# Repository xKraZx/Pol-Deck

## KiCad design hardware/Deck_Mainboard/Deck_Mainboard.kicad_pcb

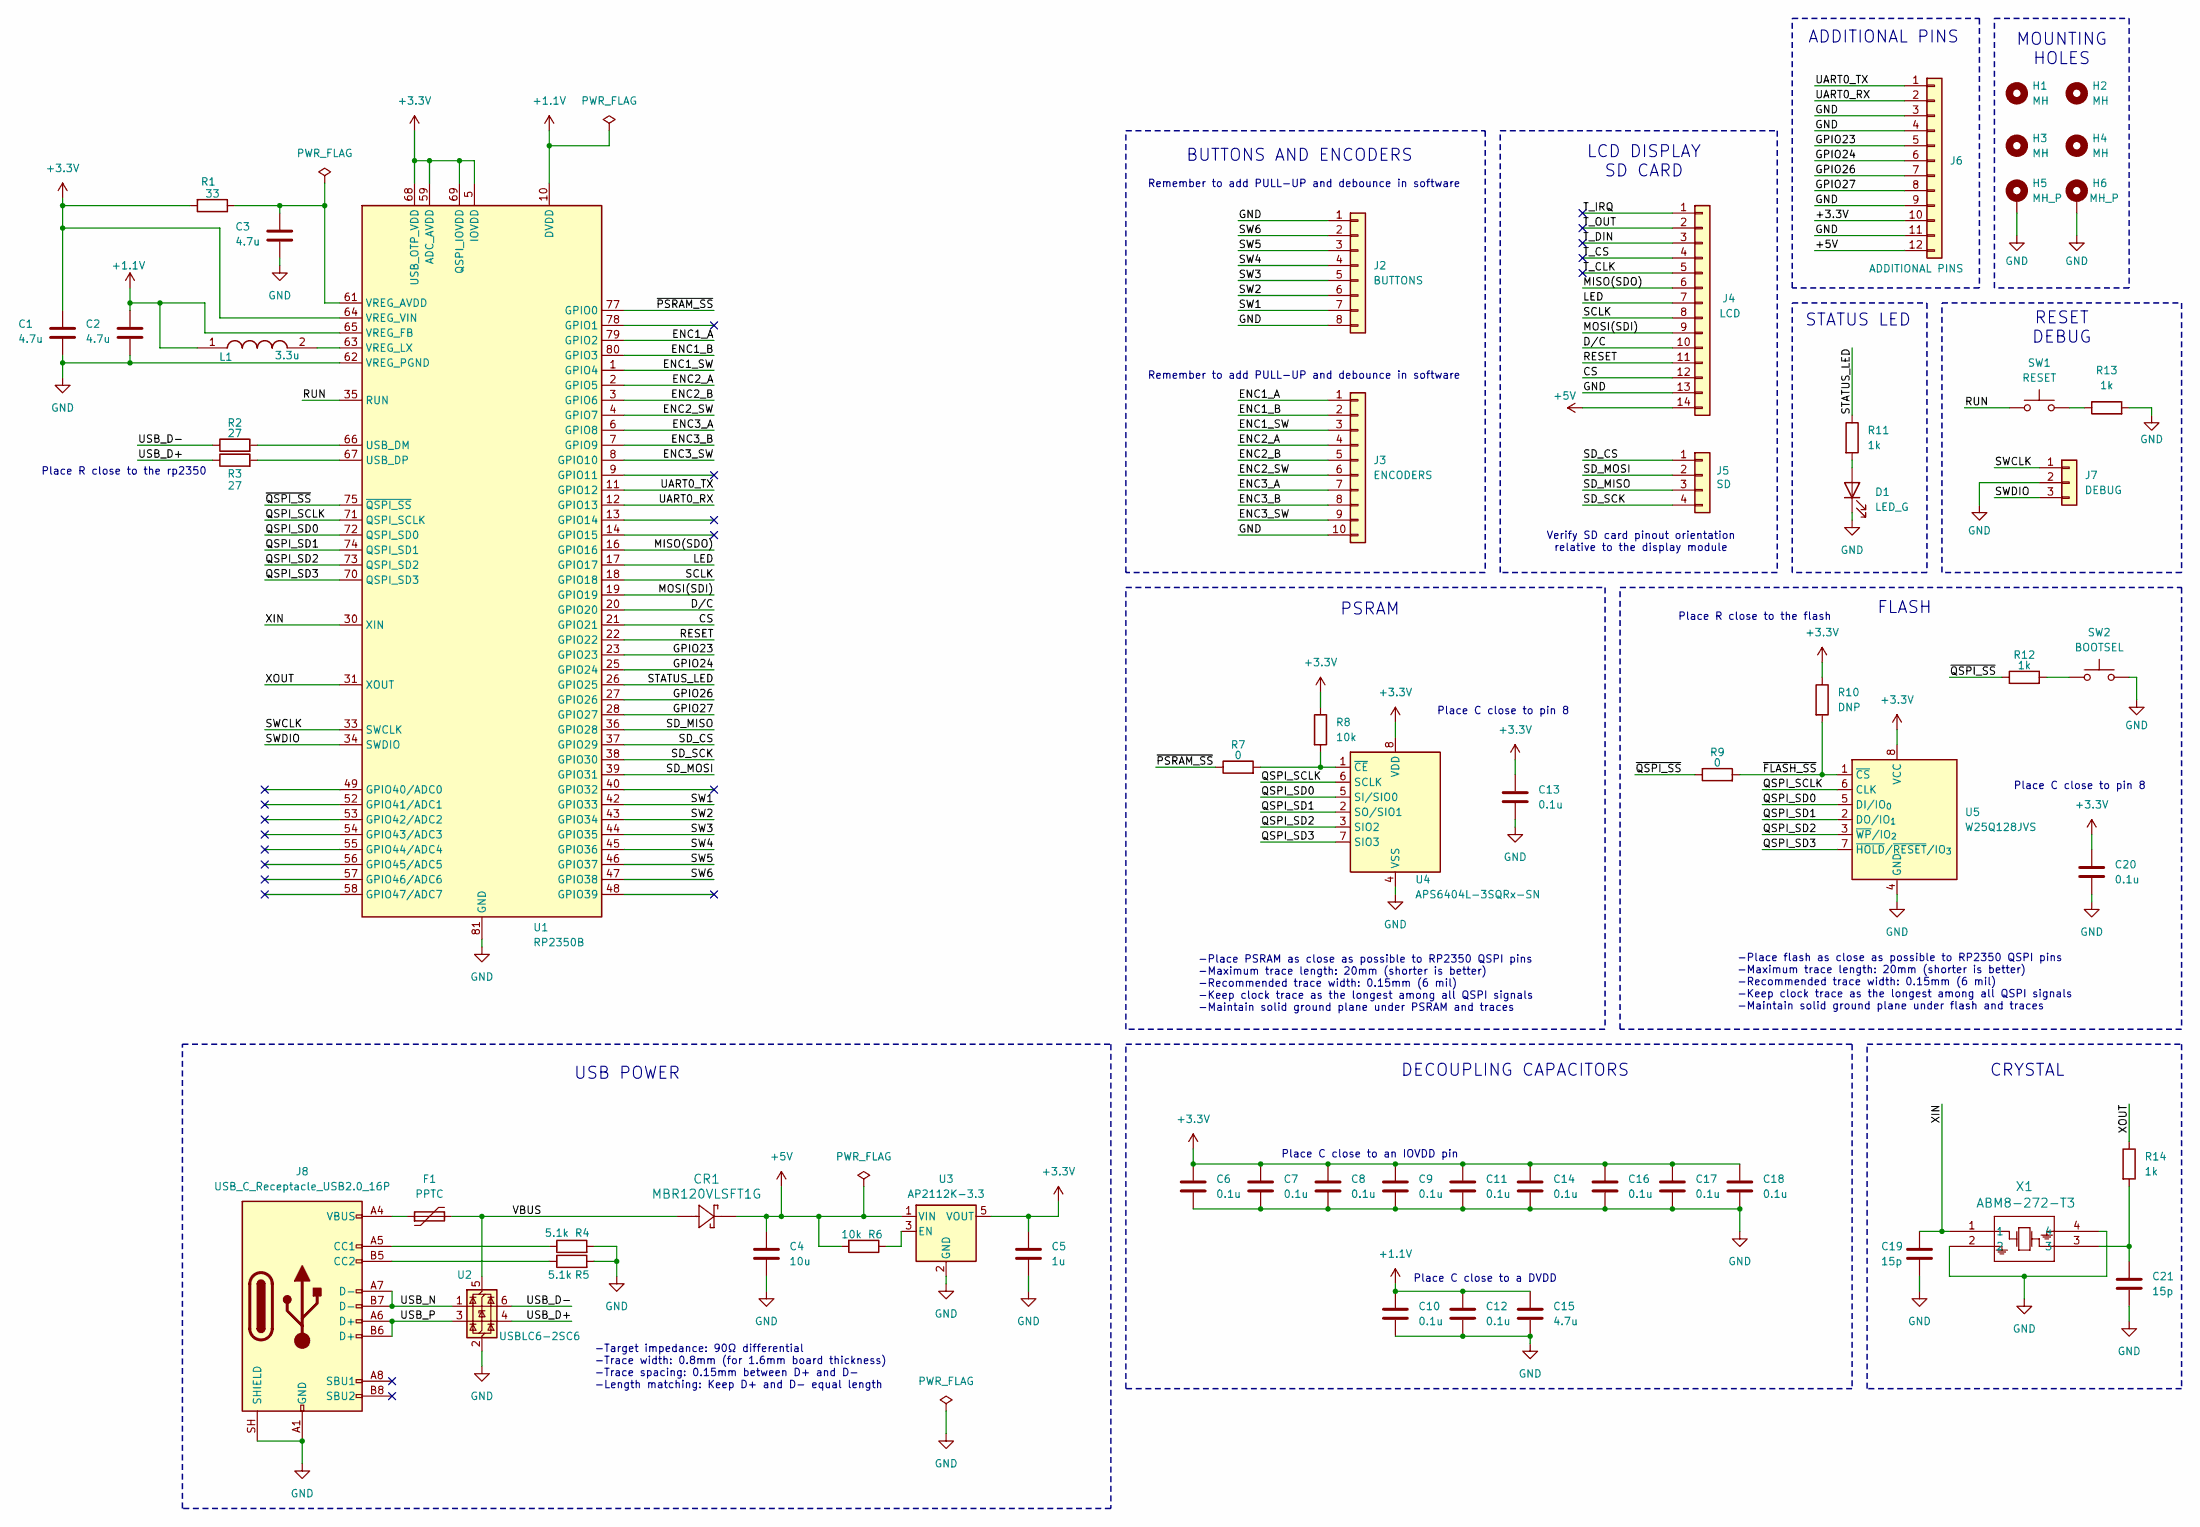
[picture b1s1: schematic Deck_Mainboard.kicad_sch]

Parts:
C1, C2, C3, C15: 4.7u; C_0402_1005Metric_Pad0.74x0.62mm_HandSolder
C4: 10u; C_0402_1005Metric_Pad0.74x0.62mm_HandSolder
C5: 1u; C_0402_1005Metric_Pad0.74x0.62mm_HandSolder
C6, C7, C8, C9, C10, C11, C12, C13, C14, C16, C17, C18, C20: 0.1u; C_0402_1005Metric_Pad0.74x0.62mm_HandSolder
C19, C21: 15p; C_0402_1005Metric_Pad0.74x0.62mm_HandSolder
CR1: MBR120VLSFT1G
D1: LED_G; LED_0603_1608Metric_Pad1.05x0.95mm_HandSolder
F1: PPTC; Fuse_1812_4532Metric_Pad1.30x3.40mm_HandSolder
H1, H2, H3, H4: MH; MountingHole_3.2mm_M3
H5, H6: MH_P; MountingHole_3.2mm_M3_Pad
J2: BUTTONS; PinHeader_1x08_P2.54mm_Vertical
J3: ENCODERS; PinHeader_1x10_P2.54mm_Vertical
J4: LCD; PinHeader_1x14_P2.54mm_Vertical
J5: SD; PinHeader_1x04_P2.54mm_Vertical
J6: ADDITIONAL PINS; PinHeader_1x12_P2.54mm_Vertical
J7: DEBUG; PinHeader_1x03_P2.54mm_Vertical
J8: USB_C_Receptacle_USB2.0_16P; USB_C_vertical
L1: 3.3u; AOTAB201610S3R3101T; Manufacturer_Part_Number AOTA-B201610S3R3-101-T
R1: 33; R_0402_1005Metric_Pad0.72x0.64mm_HandSolder
R2, R3: 27; R_0402_1005Metric_Pad0.72x0.64mm_HandSolder
R4, R5: 5.1k; R_0402_1005Metric_Pad0.72x0.64mm_HandSolder
R6, R8: 10k; R_0402_1005Metric_Pad0.72x0.64mm_HandSolder
R7, R9: 0; R_0402_1005Metric_Pad0.72x0.64mm_HandSolder
R10: DNP; R_0402_1005Metric_Pad0.72x0.64mm_HandSolder
R11, R12, R13, R14: 1k; R_0402_1005Metric_Pad0.72x0.64mm_HandSolder
SW1: RESET; SW_Push_1P1T_NO_E-Switch_TL3301NxxxxxG
SW2: BOOTSEL; SW_Push_1P1T_NO_E-Switch_TL3301NxxxxxG
U1: RP2350B; QFN-80-1EP_10x10mm_P0.4mm_EP3.4x3.4mm
U2: USBLC6-2SC6; SOT-23-6
U3: AP2112K-3.3; SOT-23-5
U4: APS6404L-3SQRx-SN; SOIC-8_3.9x4.9mm_P1.27mm
U5: W25Q128JVS; SOIC-8_5.3x5.3mm_P1.27mm
X1: ABM8-272-T3; ABM8-272-T3_ABR

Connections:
+1.1V: C2.1, C10.1, C12.1, C15.1, L1.1, U1.10 (DVDD), U1.32 (DVDD), U1.51 (DVDD), U1.65 (VREG_FB)
+3.3V: C1.1, C5.1, C6.1, C7.1, C8.1, C9.1, C11.1, C13.1, C14.1, C16.1, C17.1, C18.1, C20.1, J6.10, R1.2, R8.1, R10.1, U1.5 (IOVDD), U1.15 (IOVDD), U1.24 (IOVDD), U1.29 (IOVDD), U1.41 (IOVDD), U1.50 (IOVDD), U1.59 (ADC_AVDD), U1.60 (IOVDD), U1.64 (VREG_VIN), U1.68 (USB_OTP_VDD), U1.69 (QSPI_IOVDD), U1.76 (IOVDD), U3.5 (VOUT), U4.8 (VDD), U5.8 (VCC)
+5V: C4.1, CR1.1, J4.14, J6.12, R6.2, U3.1 (VIN)
/CS: J4.12, U1.21 (GPIO21)
/D/C: J4.10, U1.20 (GPIO20)
/ENC1_A: J3.1, U1.79 (GPIO2)
/ENC1_B: J3.2, U1.80 (GPIO3)
/ENC1_SW: J3.3, U1.1 (GPIO4)
/ENC2_A: J3.4, U1.2 (GPIO5)
/ENC2_B: J3.5, U1.3 (GPIO6)
/ENC2_SW: J3.6, U1.4 (GPIO7)
/ENC3_A: J3.7, U1.6 (GPIO8)
/ENC3_B: J3.8, U1.7 (GPIO9)
/ENC3_SW: J3.9, U1.8 (GPIO10)
/GPIO23: J6.5, U1.23 (GPIO23)
/GPIO24: J6.6, U1.25 (GPIO24)
/GPIO26: J6.7, U1.27 (GPIO26)
/GPIO27: J6.8, U1.28 (GPIO27)
/LED: J4.7, U1.17 (GPIO17)
/MISO(SDO): J4.6, U1.16 (GPIO16)
/MOSI(SDI): J4.9, U1.19 (GPIO19)
/QSPI_SCLK: U1.71 (QSPI_SCLK), U4.6 (SCLK), U5.6 (CLK)
/QSPI_SD0: U1.72 (QSPI_SD0), U4.5 (SI/SIO0), U5.5 (DI/IO_{0})
/QSPI_SD1: U1.74 (QSPI_SD1), U4.2 (SO/SIO1), U5.2 (DO/IO_{1})
/QSPI_SD2: U1.73 (QSPI_SD2), U4.3 (SIO2), U5.3 (~WP/IO_{2})
/QSPI_SD3: U1.70 (QSPI_SD3), U4.7 (SIO3), U5.7 (~HOLD/~RESET/IO_{3})
/RESET: J4.11, U1.22 (GPIO22)
/RUN: SW1.1, U1.35 (RUN)
/SCLK: J4.8, U1.18 (GPIO18)
/SD_CS: J5.1, U1.37 (GPIO29)
/SD_MISO: J5.3, U1.36 (GPIO28)
/SD_MOSI: J5.2, U1.39 (GPIO31)
/SD_SCK: J5.4, U1.38 (GPIO30)
/STATUS_LED: R11.1, U1.26 (GPIO25)
/SW1: J2.7, U1.42 (GPIO33)
/SW2: J2.6, U1.43 (GPIO34)
/SW3: J2.5, U1.44 (GPIO35)
/SW4: J2.4, U1.45 (GPIO36)
/SW5: J2.3, U1.46 (GPIO37)
/SW6: J2.2, U1.47 (GPIO38)
/SWCLK: J7.1, U1.33 (SWCLK)
/SWDIO: J7.3, U1.34 (SWDIO)
/T_CLK: J4.5
/T_CS: J4.4
/T_DIN: J4.3
/T_IRQ: J4.1
/T_OUT: J4.2
/UART0_RX: J6.2, U1.12 (GPIO13)
/UART0_TX: J6.1, U1.11 (GPIO12)
/USB_D+: R3.1, U2.4 (I/O2)
/USB_D-: R2.1, U2.6 (I/O1)
/USB_N: J8.A7 (D-), J8.B7 (D-), U2.1 (I/O1)
/USB_P: J8.A6 (D+), J8.B6 (D+), U2.3 (I/O2)
/VBUS: CR1.2, F1.2, U2.5 (VBUS)
/XIN: C19.1, U1.30 (XIN), X1.1
/XOUT: R14.1, U1.31 (XOUT)
/~FLASH_SS: R9.2, R10.2, U5.1 (~CS)
/~PSRAM_SS: R7.1, U1.77 (GPIO0)
/~QSPI_SS: R9.1, R12.1, U1.75 (~QSPI_SS)
GND: C1.2, C2.2, C3.2, C4.2, C5.2, C6.2, C7.2, C8.2, C9.2, C10.2, C11.2, C12.2, C13.2, C14.2, C15.2, C16.2, C17.2, C18.2, C19.2, C20.2, C21.2, D1.1 (K), H5.1 (1_1), H6.1 (1_1), J2.1, J2.8, J3.10, J4.13, J6.3, J6.4, J6.9, J6.11, J7.2, J8.A1 (GND), J8.A12 (GND), J8.B1 (GND), J8.B12 (GND), J8.SH (SHIELD), R4.2, R5.2, R13.2, SW2.2, U1.62 (VREG_PGND), U1.81 (GND), U2.2 (GND), U3.2 (GND), U4.4 (VSS), U5.4 (GND), X1.2, X1.4
unnamed: C21.1, R14.2, X1.3
unnamed: D1.2 (A), R11.2
unnamed: F1.1, J8.A4 (VBUS), J8.A9 (VBUS), J8.B4 (VBUS), J8.B9 (VBUS)
unnamed: J8.A5 (CC1), R4.1
unnamed: J8.B5 (CC2), R5.1
unnamed: R12.2, SW2.1
unnamed: R13.1, SW1.2
unnamed: R2.2, U1.66 (USB_DM)
unnamed: R3.2, U1.67 (USB_DP)
unnamed: C3.1, R1.1, U1.61 (VREG_AVDD)
unnamed: L1.2, U1.63 (VREG_LX)
unnamed: R6.1, U3.3 (EN)
unnamed: R7.2, R8.2, U4.1 (~CE)

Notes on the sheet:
-Place PSRAM as close as possible to RP2350 QSPI pins -Maximum trace length: 20mm (shorter is better) -Recommended trace width: 0.15mm (6 mil) -Keep clock trace as the longest among all QSPI signals -Maintain solid ground plane under PSRAM and traces
ADDITIONAL PINS
USB POWER
LCD DISPLAY SD CARD
BUTTONS AND ENCODERS
Place R close to the rp2350
Verify SD card pinout orientation relative to the display module
CRYSTAL
Place C close to a DVDD
FLASH
PSRAM
Place R close to the flash
RESET DEBUG
-Place flash as close as possible to RP2350 QSPI pins -Maximum trace length: 20mm (shorter is better) -Recommended trace width: 0.15mm (6 mil) -Keep clock trace as the longest among all QSPI signals -Maintain solid ground plane under flash and traces
MOUNTING HOLES
Remember to add PULL-UP and debounce in software
Place C close to pin 8
DECOUPLING CAPACITORS
-Target impedance: 90Ω differential -Trace width: 0.8mm (for 1.6mm board thickness) -Trace spacing: 0.15mm between D+ and D- -Length matching: Keep D+ and D- equal length
STATUS LED
Place C close to an IOVDD pin

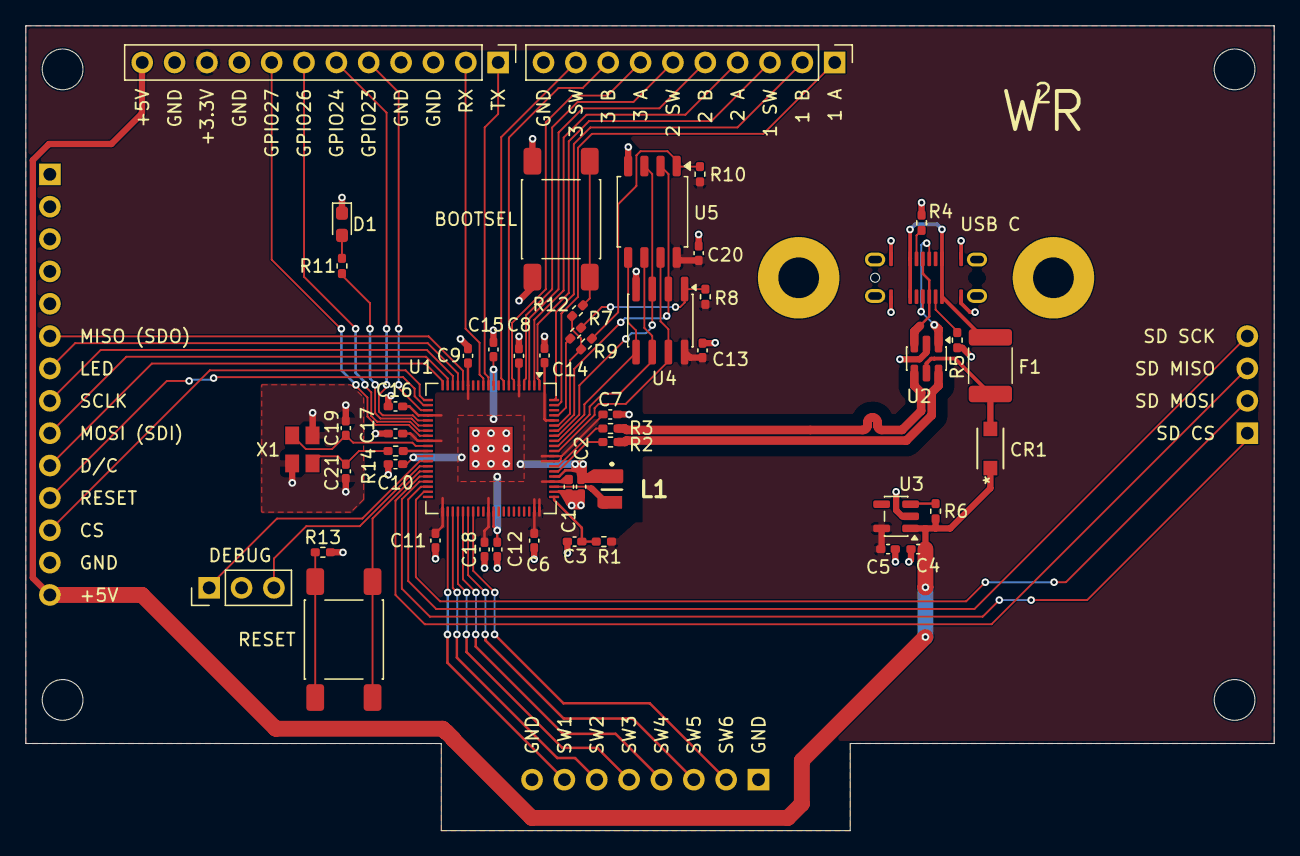
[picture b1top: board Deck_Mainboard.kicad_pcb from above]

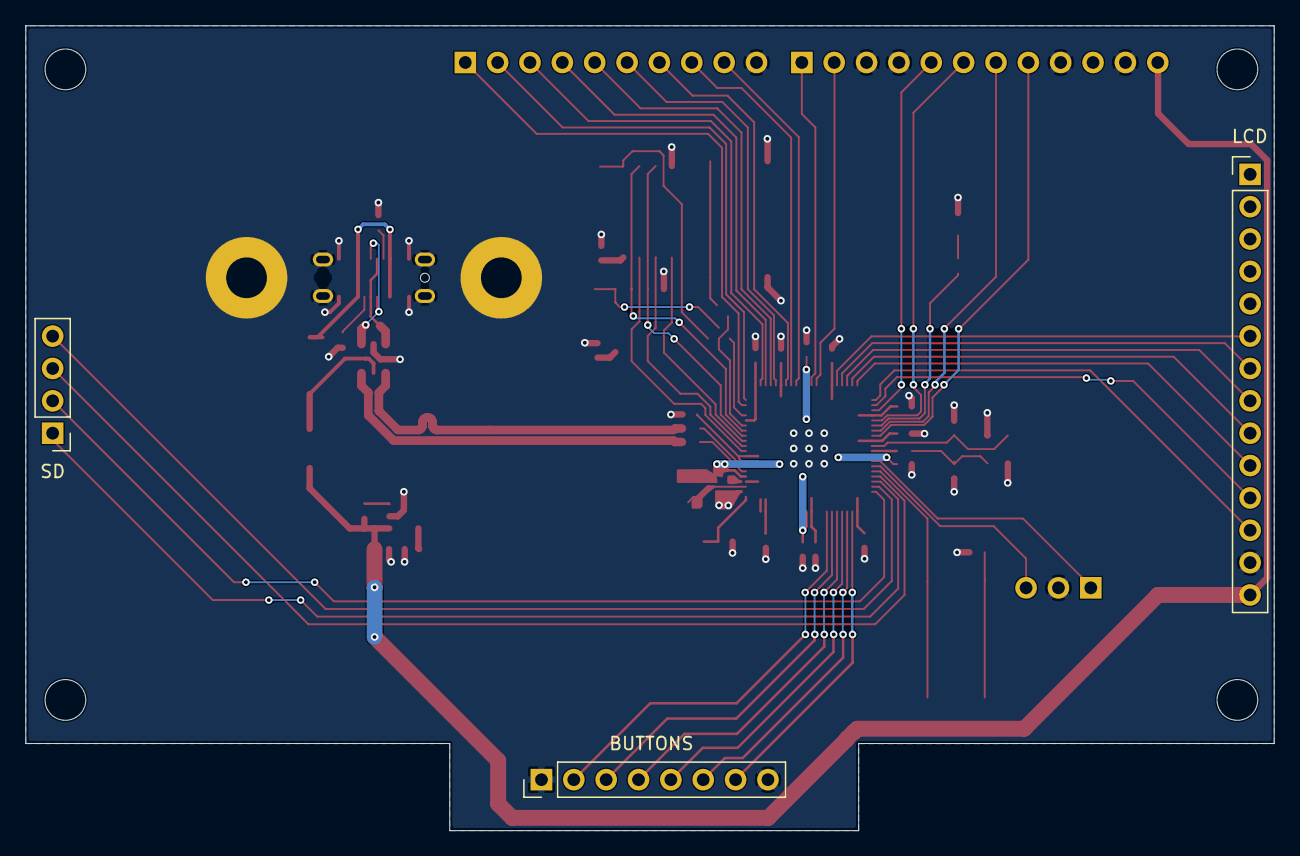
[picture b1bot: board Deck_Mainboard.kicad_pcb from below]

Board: 2 copper layers, 98.0 x 63.2 mm, 60 parts (3 on the bottom side), 68 nets.

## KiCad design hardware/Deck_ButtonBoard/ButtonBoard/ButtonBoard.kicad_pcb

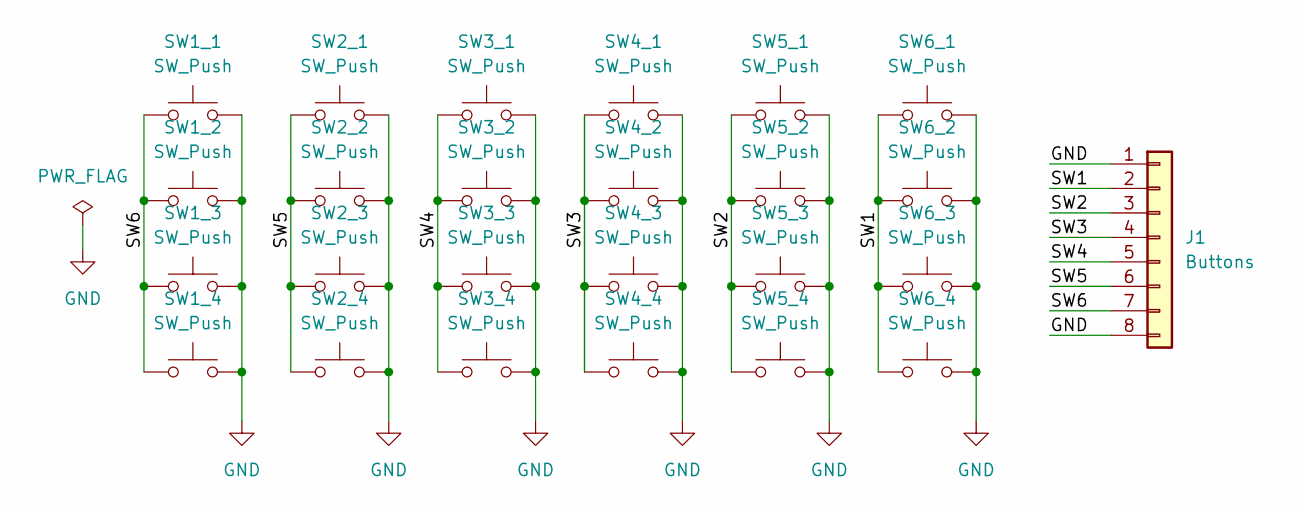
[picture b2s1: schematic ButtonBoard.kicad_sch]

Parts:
J1: Buttons; PinSocket_1x08_P2.54mm_Vertical
SW1_1, SW1_2, SW1_3, SW1_4, SW2_1, SW2_2, SW2_3, SW2_4, SW3_1, SW3_2, SW3_3, SW3_4, SW4_1, SW4_2, SW4_3, SW4_4, SW5_1, SW5_2, SW5_3, SW5_4, SW6_1, SW6_2, SW6_3, SW6_4: SW_Push; SW_Tactile_SPST_NO_Straight_CK_PTS636Sx25SMTRLFS

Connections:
/SW1: J1.2, SW6_1.1, SW6_2.1, SW6_3.1, SW6_4.1
/SW2: J1.3, SW5_1.1, SW5_2.1, SW5_3.1, SW5_4.1
/SW3: J1.4, SW4_1.1, SW4_2.1, SW4_3.1, SW4_4.1
/SW4: J1.5, SW3_1.1, SW3_2.1, SW3_3.1, SW3_4.1
/SW5: J1.6, SW2_1.1, SW2_2.1, SW2_3.1, SW2_4.1
/SW6: J1.7, SW1_1.1, SW1_2.1, SW1_3.1, SW1_4.1
GND: J1.1, J1.8, SW1_1.2, SW1_2.2, SW1_3.2, SW1_4.2, SW2_1.2, SW2_2.2, SW2_3.2, SW2_4.2, SW3_1.2, SW3_2.2, SW3_3.2, SW3_4.2, SW4_1.2, SW4_2.2, SW4_3.2, SW4_4.2, SW5_1.2, SW5_2.2, SW5_3.2, SW5_4.2, SW6_1.2, SW6_2.2, SW6_3.2, SW6_4.2

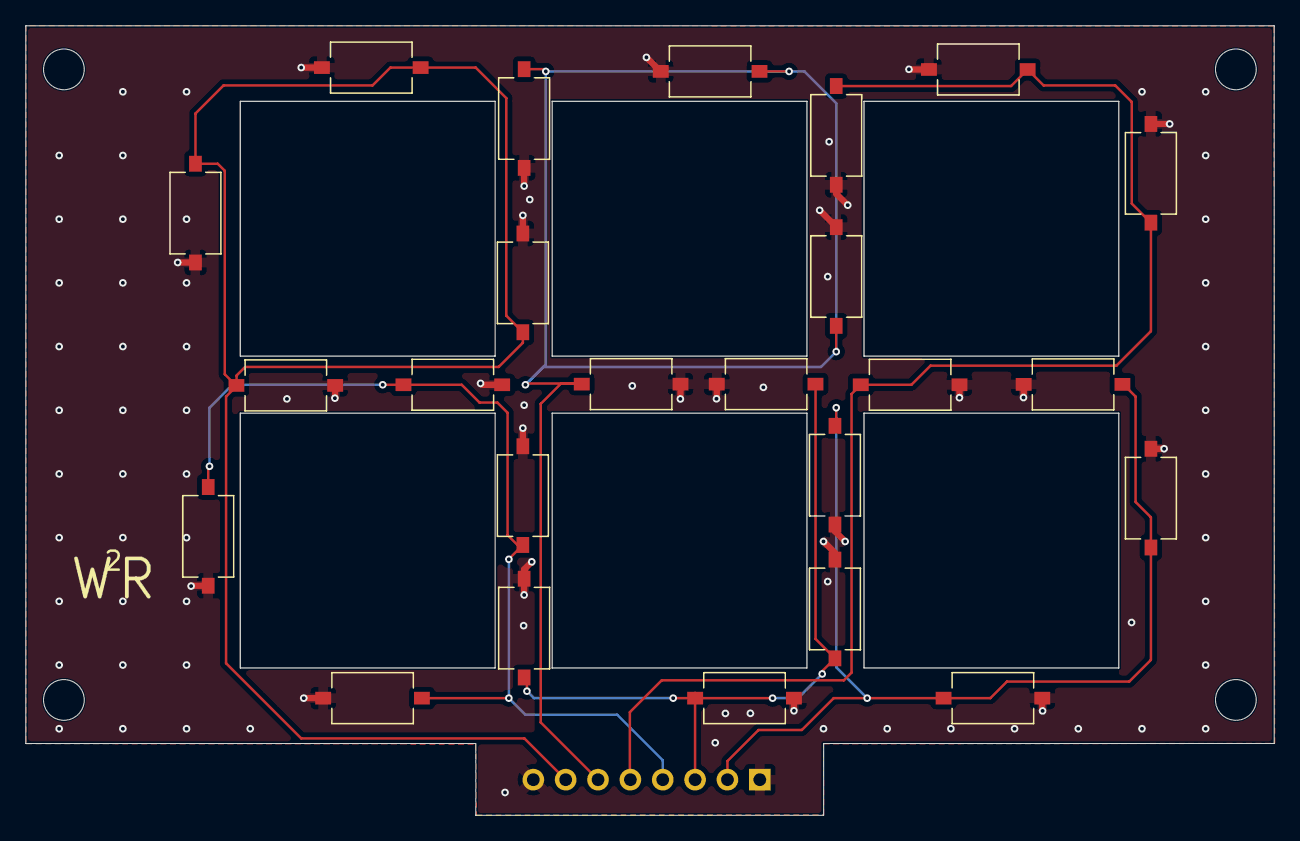
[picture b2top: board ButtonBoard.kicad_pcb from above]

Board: 2 copper layers, 98.0 x 62.0 mm, 29 parts (1 on the bottom side), 7 nets.

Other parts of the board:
H1, H2, H3, H4: MH; MountingHole_3.2mm_M3

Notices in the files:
parts and their libraries:
Copyright 2016 Accelerated Designs. All rights reserved.
